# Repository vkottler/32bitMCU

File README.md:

# 32bitMCU
Open source development of microcontroller RTOS, including driver implementations.

## TODO

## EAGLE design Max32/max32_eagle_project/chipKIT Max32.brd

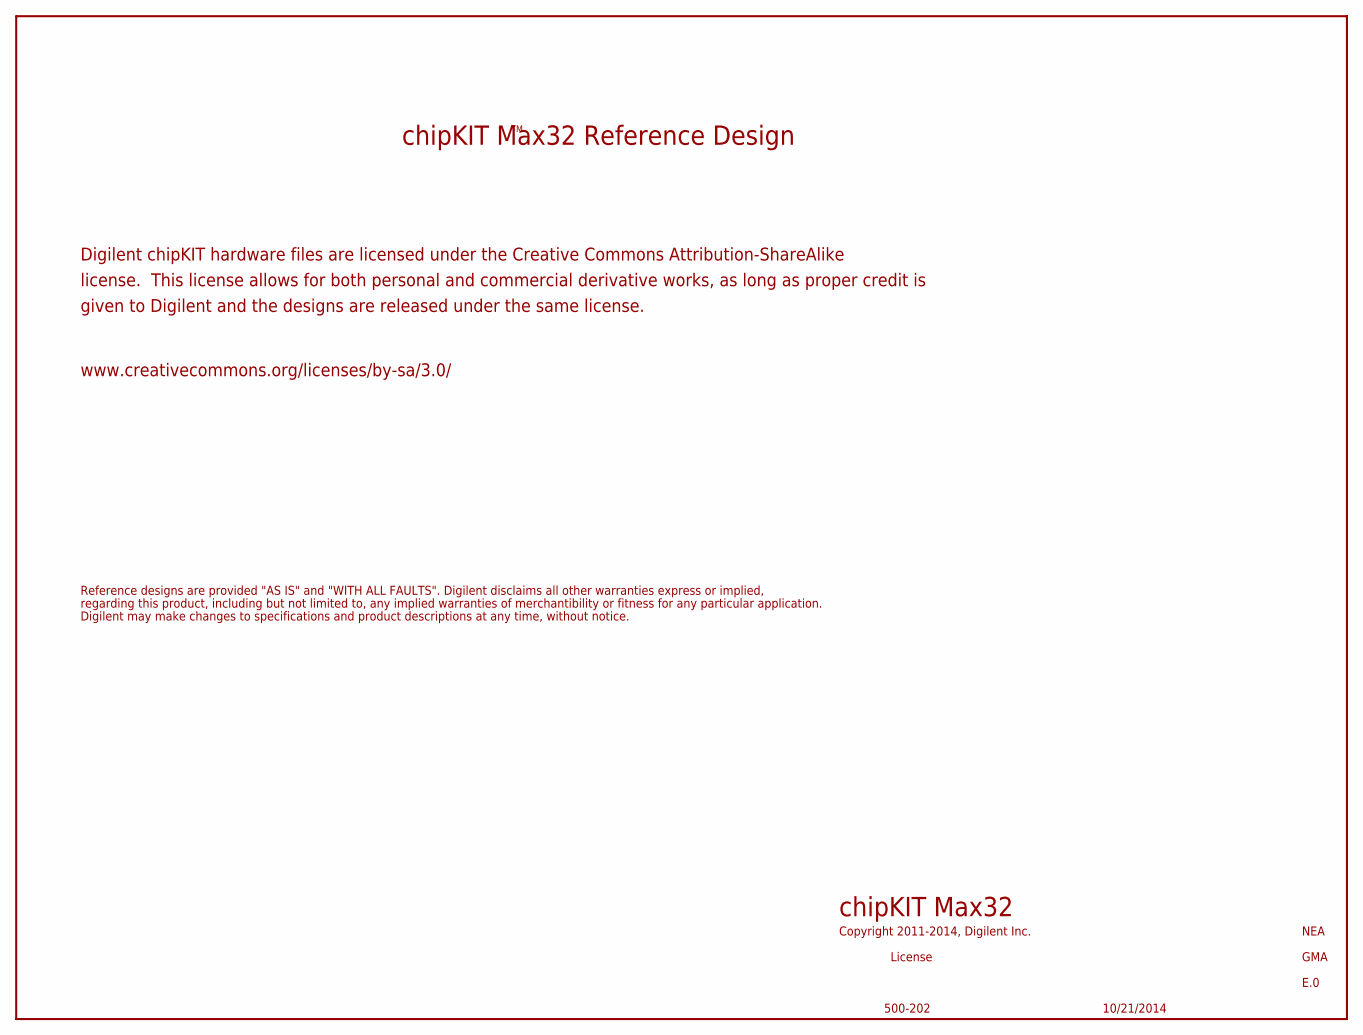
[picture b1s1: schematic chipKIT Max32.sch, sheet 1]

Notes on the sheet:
Digilent chipKIT hardware files are licensed under the Creative Commons Attribution-ShareAlike
license. This license allows for both personal and commercial derivative works, as long as proper credit is
given to Digilent and the designs are released under the same license.
chipKIT Max32 Reference Design
Reference designs are provided "AS IS" and "WITH ALL FAULTS". Digilent disclaims all other warranties express or implied,
regarding this product, including but not limited to, any implied warranties of merchantibility or fitness for any particular application.
Digilent may make changes to specifications and product descriptions at any time, without notice.
www.creativecommons.org/licenses/by-sa/3.0/
Copyright 2011-2014, Digilent Inc.
NEA
GMA
License
500-202
chipKIT Max32
E.0
10/21/2014

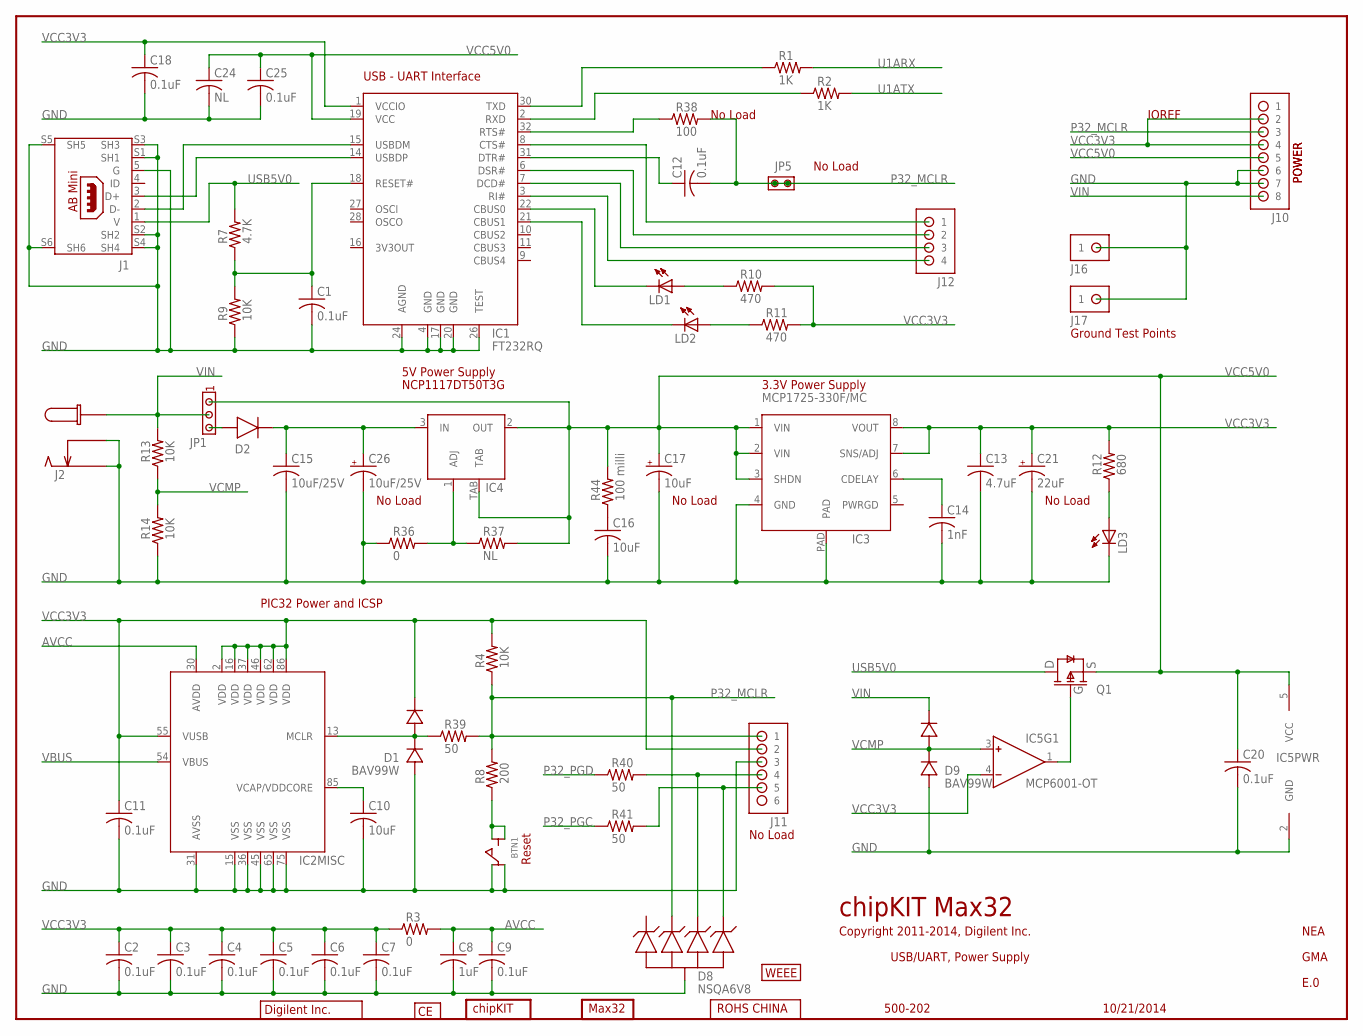
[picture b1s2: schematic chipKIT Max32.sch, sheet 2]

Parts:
BTN1: SW-P8008
C1, C2, C3, C4, C5, C6, C7, C9, C11, C12, C18, C25: 0.1uF; C0402S
C8: 1uF; C0402S
C10, C16: 10uF; C0603S
C13: 4.7uF; C0603S
C14: 1nF; C0402S
C15: 10uF/25V; C0805S
C17: 10uF; CPOL3216
C20: 0.1uF; C0402
C21: 22uF; CPOL3216
C24: NL; C0603S
C26: 10uF/25V; CPOL3216
D1, D9: BAV99W; SOT-323
D2: B220A; SMA
D8: NSQA6V8; SOT-323-5
IC1: FT232RQ; QFN32
IC2: PIC32MX7X5FL-PT; TQ100-PT
IC3: MCP1725-330F/MC; DFN8-MC
IC4: NCP1117DT50T3G; SOT223
IC5: MCP6001-OT; SOT23-5-OT
J1: USB-AB-MINI
J2: CON-COAX-KLD0202-S; KLD-0202S
J10: ST Female; HDR-1X8
J11: No Load; HDR-1X6_OFFSET
J12: HDR-1X4
J16, J17: HDR-1X1
JP1: JPR-1X3
JP5: No Load; JPR-1X2
LD1, LD2, LD3: LED-S0603-RED; D0603
LOGO1: ROHS-CHINA-INV; ROHS_CHINA_INV_LOGO
LOGO2: WEEE-L; WEEE_LOGO2
LOGO4: MAX32_LOGO
LOGO5: CHIPKIT; CHIPKIT_LOGO
LOGO6: CE; CE_LOGO
LOGO7: DIGILENT_INC-BT-1500; DIGILENT_BEYOND_1500_LOGO
Q1: FDN340P; SOT23
R1, R2: 1K; R0402S
R3: 0; R0603
R4, R9, R13, R14: 10K; R0402S
R7: 4.7K; R0402S
R8: 200; R0402S
R10, R11: 470; R0402S
R12: 680; R0402S
R36: 0; R0402S
R37: NL; R0402S
R38: 100; R0402S
R39, R40, R41: 50; R0402S
R44: 100 milli; R0603S

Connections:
AVCC: C8.1, C9.1, IC2.30 (AVDD), R3.2
GND: BTN1.1A, BTN1.2A, C1.2, C2.2, C3.2, C4.2, C5.2, C6.2, C7.2, C8.2, C9.2, C10.2, C11.2, C13.2, C14.2, C15.2, C16.2, C17.-, C18.2, C20.2, C21.-, C24.2, C25.2, C26.-, D1.1 (CAT), D8.2 (COM), D9.1 (CAT), IC1.4 (GND), IC1.17 (GND), IC1.20 (GND), IC1.24 (AGND), IC1.26 (TEST), IC2.15 (VSS), IC2.31 (AVSS), IC2.36 (VSS), IC2.45 (VSS), IC2.65 (VSS), IC2.75 (VSS), IC3.4 (GND), IC3.PAD, IC5.2 (GND), J1.5 (G), J1.S1 (SH1), J1.S2 (SH2), J1.S3 (SH3), J1.S4 (SH4), J1.S5 (SH5), J1.S6 (SH6), J2.2, J2.3, J10.6, J10.7, J11.3, J16.1, J17.1, LD3.C, R9.1, R14.1, R36.1; also elsewhere on the board
unnamed: IC1.14 (USBDP), J1.3 (D+)
unnamed: IC1.15 (USBDM), J1.2 (D-)
unnamed: IC4.1 (ADJ), R36.2, R37.1
unnamed: IC1.30 (TXD), R1.1
unnamed: C10.1, IC2.85 (VCAP/VDDCORE)
unnamed: IC1.2 (RXD), R2.1
unnamed: C12.1, IC1.31 (DTR#)
unnamed: BTN1.1B, BTN1.2B, R8.1
unnamed: IC1.8 (CTS#), J12.1
unnamed: IC1.6 (DSR#), J12.2
unnamed: IC1.7 (DCD#), J12.3
unnamed: IC1.3 (RI#), J12.4
unnamed: IC1.22 (CBUS0), LD1.C
unnamed: IC1.21 (CBUS1), LD2.C
unnamed: LD2.A, R11.1
unnamed: LD1.A, R10.1
unnamed: C14.1, IC3.6 (CDELAY)
unnamed: LD3.A, R12.1
unnamed: D2.A, JP1.3
unnamed: IC5.1 (OUT), Q1.1 (G)
unnamed: C15.1, C26.+, D2.C, IC4.3 (IN)
unnamed: C16.1, R44.1
unnamed: C1.1, IC1.18 (RESET#), R7.1, R9.2
unnamed: D8.4 (D3), J11.4, R40.2
unnamed: IC1.32 (RTS#), R38.1
unnamed: D8.5 (D4), J11.5, R41.2
unnamed: D1.3 (COM), IC2.13 (MCLR), R39.1
P32_MCLR: C12.2, D8.3 (D2), J10.3, J11.1, JP5.1, JP5.2, R4.1, R8.2, R38.2, R39.2
P32_PGC: R41.1; also elsewhere on the board
P32_PGD: R40.1; also elsewhere on the board
U1ARX: R1.2; also elsewhere on the board
U1ATX: R2.2; also elsewhere on the board
USB5V0: J1.1 (V), Q1.3 (D), R7.2
VBUS: IC2.54 (VBUS); also elsewhere on the board
VCC3V3: C2.1, C3.1, C4.1, C5.1, C6.1, C7.1, C11.1, C13.1, C18.1, C21.+, D1.2 (AN), IC1.1 (VCCIO), IC2.2 (VDD), IC2.16 (VDD), IC2.37 (VDD), IC2.46 (VDD), IC2.55 (VUSB), IC2.62 (VDD), IC2.86 (VDD), IC3.7 (SNS/ADJ), IC3.8 (VOUT), IC5.4 (IN-), J10.2, J10.4, J11.2, R3.1, R4.2, R10.2, R11.2, R12.2; also elsewhere on the board
VCC5V0: C17.+, C20.1, C24.1, C25.1, IC1.19 (VCC), IC3.1 (VIN), IC3.2 (VIN), IC3.3 (SHDN), IC4.2 (OUT), IC4.TAB, IC5.5 (VCC), J10.5, JP1.1, Q1.2 (S), R37.2, R44.2; also elsewhere on the board
VCMP: D9.3 (COM), IC5.3 (IN+), R13.1, R14.2
VIN: D9.2 (AN), J2.1, J10.8, JP1.2, R13.2

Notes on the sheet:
Reset
POWER
NCP1117DT50T3G
chipKIT Max32
Copyright 2011-2014, Digilent Inc.
USB/UART, Power Supply
NEA
GMA
E.0
10/21/2014
USB - UART Interface
PIC32 Power and ICSP
5V Power Supply
3.3V Power Supply
500-202
No Load
Ground Test Points
IOREF

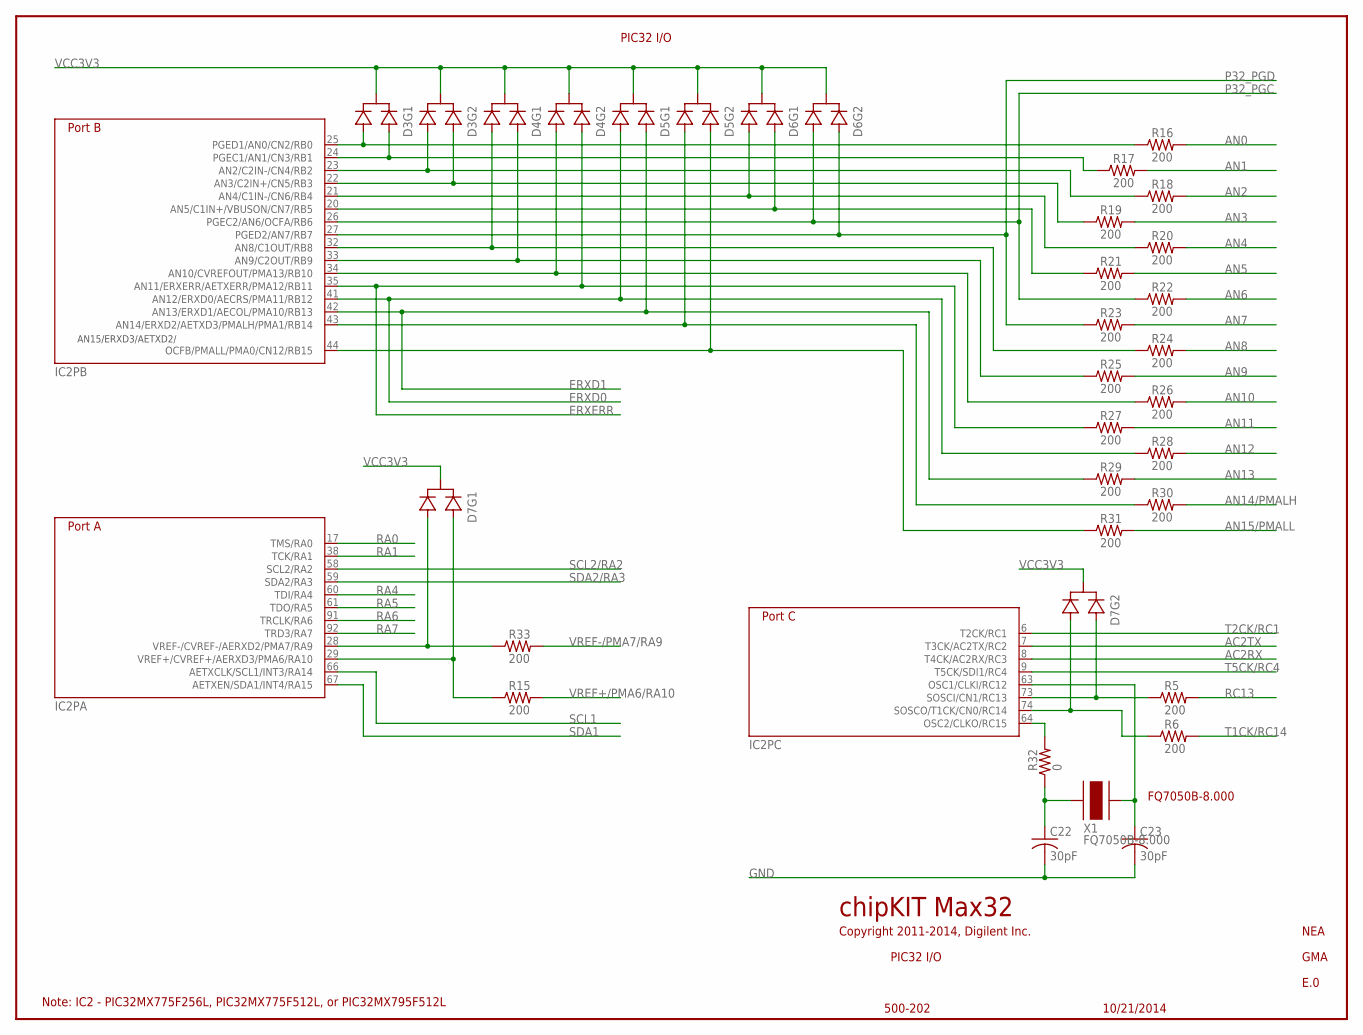
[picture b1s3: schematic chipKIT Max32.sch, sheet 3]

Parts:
C22, C23: 30pF; C0402S
D3, D4, D5, D6, D7: BAV70S; SOT-363
IC2: PIC32MX7X5FL-PT; TQ100-PT
R5, R6, R15, R16, R17, R18, R19, R20, R21, R22, R23, R24, R25, R26, R27, R28, R29, R30, R31, R33: 200; R0402S
R32: 0; R0402S
X1: FQ7050B-8.000; FQ7050B

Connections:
AC2RX: IC2.8 (T4CK/AC2RX/RC3); also elsewhere on the board
AC2TX: IC2.7 (T3CK/AC2TX/RC2); also elsewhere on the board
AN0: R16.2; also elsewhere on the board
AN0-R: D3.1 (A1), IC2.25 (PGED1/AN0/CN2/RB0), R16.1
AN1: R17.2; also elsewhere on the board
AN1-R: D3.2 (A2), IC2.24 (PGEC1/AN1/CN3/RB1), R17.1
AN2: R18.2; also elsewhere on the board
AN3: R19.2; also elsewhere on the board
AN4: R20.2; also elsewhere on the board
AN5: R21.2; also elsewhere on the board
AN6: R22.2; also elsewhere on the board
AN7: R23.2; also elsewhere on the board
AN8: R24.2; also elsewhere on the board
AN9: R25.2; also elsewhere on the board
AN10: R26.2; also elsewhere on the board
AN11: R27.2; also elsewhere on the board
AN12: R28.2; also elsewhere on the board
AN13: R29.2; also elsewhere on the board
AN14/PMALH: R30.2; also elsewhere on the board
AN15/PMALL: R31.2; also elsewhere on the board
ERXD0: D5.1 (A1), IC2.41 (AN12/ERXD0/AECRS/PMA11/RB12), R28.1; also elsewhere on the board
ERXD1: D5.2 (A2), IC2.42 (AN13/ERXD1/AECOL/PMA10/RB13), R29.1; also elsewhere on the board
ERXERR: D4.5 (A2), IC2.35 (AN11/ERXERR/AETXERR/PMA12/RB11), R27.1; also elsewhere on the board
GND: C22.2, C23.2; also elsewhere on the board
unnamed: D7.5 (A2), IC2.73 (SOSCI/CN1/RC13), R5.1
unnamed: D7.4 (A1), IC2.74 (SOSCO/T1CK/CN0/RC14), R6.1
unnamed: D7.1 (A1), IC2.28 (VREF-/CVREF-/AERXD2/PMA7/RA9), R33.1
unnamed: D7.2 (A2), IC2.29 (VREF+/CVREF+/AERXD3/PMA6/RA10), R15.1
unnamed: IC2.64 (OSC2/CLKO/RC15), R32.2
unnamed: C22.1, R32.1, X1.1
unnamed: D3.4 (A1), IC2.23 (AN2/C2IN-/CN4/RB2), R18.1
unnamed: C23.1, IC2.63 (OSC1/CLKI/RC12), X1.3 (2)
unnamed: D3.5 (A2), IC2.22 (AN3/C2IN+/CN5/RB3), R19.1
unnamed: D6.1 (A1), IC2.21 (AN4/C1IN-/CN6/RB4), R20.1
unnamed: D6.2 (A2), IC2.20 (AN5/C1IN+/VBUSON/CN7/RB5), R21.1
unnamed: D4.1 (A1), IC2.32 (AN8/C1OUT/RB8), R24.1
unnamed: D4.2 (A2), IC2.33 (AN9/C2OUT/RB9), R25.1
unnamed: D4.4 (A1), IC2.34 (AN10/CVREFOUT/PMA13/RB10), R26.1
unnamed: D5.4 (A1), IC2.43 (AN14/ERXD2/AETXD3/PMALH/PMA1/RB14), R30.1
unnamed: D5.5 (A2), IC2.44 (OCFB/PMALL/PMA0/CN12/RB15), R31.1
P32_PGC: D6.4 (A1), IC2.26 (PGEC2/AN6/OCFA/RB6), R22.1; also elsewhere on the board
P32_PGD: D6.5 (A2), IC2.27 (PGED2/AN7/RB7), R23.1; also elsewhere on the board
RA0: IC2.17 (TMS/RA0); also elsewhere on the board
RA1: IC2.38 (TCK/RA1); also elsewhere on the board
RA4: IC2.60 (TDI/RA4); also elsewhere on the board
RA5: IC2.61 (TDO/RA5); also elsewhere on the board
RA6: IC2.91 (TRCLK/RA6); also elsewhere on the board
RA7: IC2.92 (TRD3/RA7); also elsewhere on the board
RC13: R5.2; also elsewhere on the board
SCL1: IC2.66 (AETXCLK/SCL1/INT3/RA14); also elsewhere on the board
SCL2/RA2: IC2.58 (SCL2/RA2); also elsewhere on the board
SDA1: IC2.67 (AETXEN/SDA1/INT4/RA15); also elsewhere on the board
SDA2/RA3: IC2.59 (SDA2/RA3); also elsewhere on the board
T1CK/RC14: R6.2; also elsewhere on the board
T2CK/RC1: IC2.6 (T2CK/RC1); also elsewhere on the board
T5CK/RC4: IC2.9 (T5CK/SDI1/RC4); also elsewhere on the board
VCC3V3: D3.3 (K), D3.6 (K), D4.3 (K), D4.6 (K), D5.3 (K), D5.6 (K), D6.3 (K), D6.6 (K), D7.3 (K), D7.6 (K); also elsewhere on the board
VREF+/PMA6/RA10: R15.2; also elsewhere on the board
VREF-/PMA7/RA9: R33.2; also elsewhere on the board

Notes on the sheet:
PIC32 I/O
NEA
Note: IC2 - PIC32MX775F256L, PIC32MX775F512L, or PIC32MX795F512L
500-202
FQ7050B-8.000
GMA
Copyright 2011-2014, Digilent Inc.
chipKIT Max32
E.0
10/21/2014

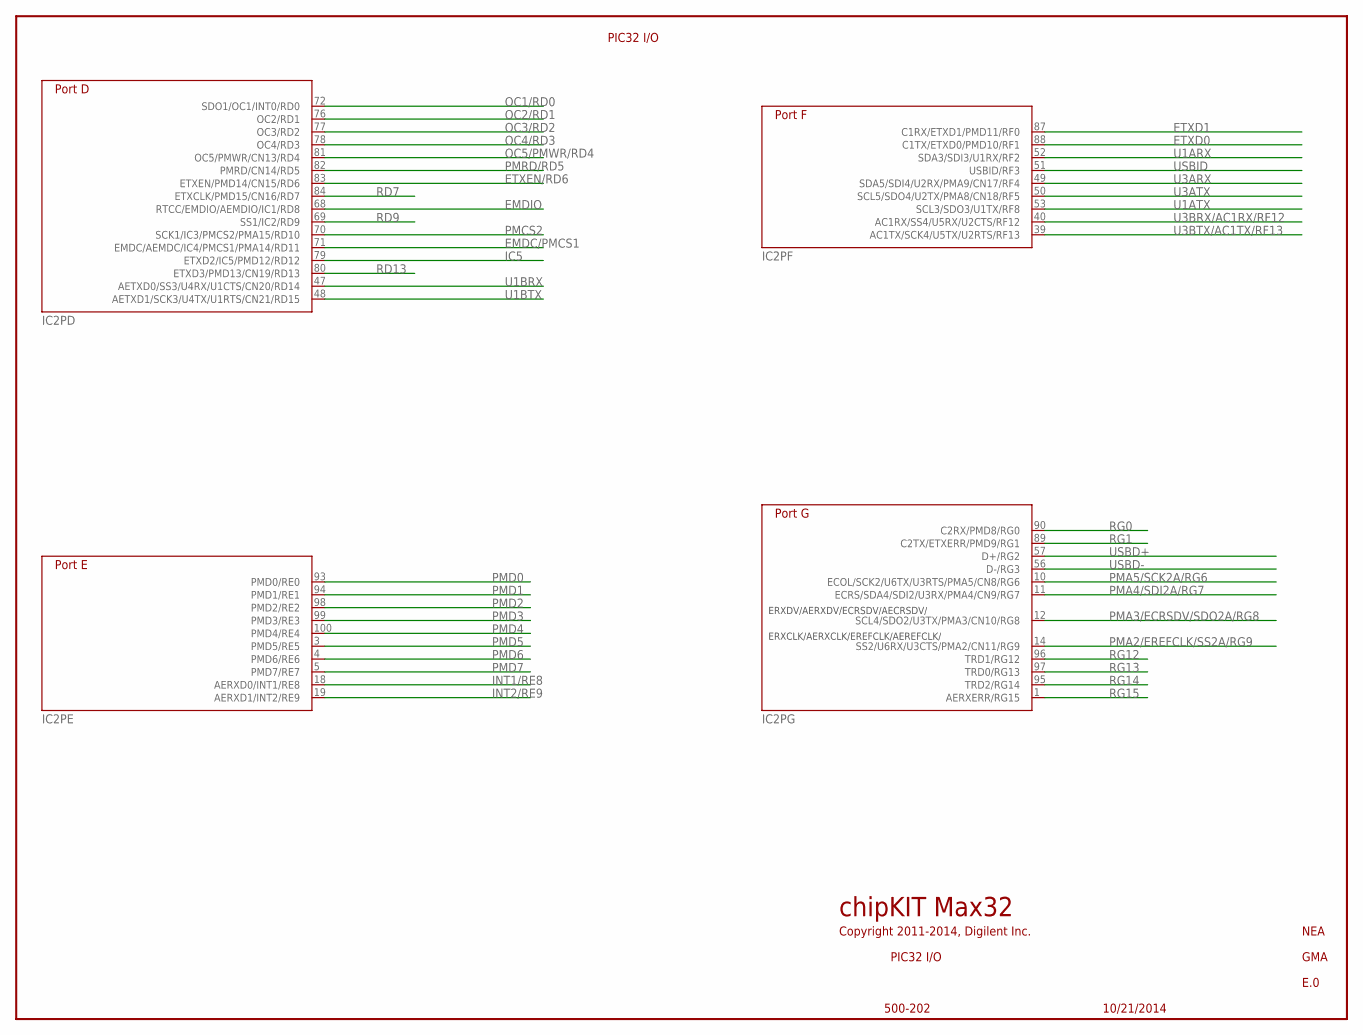
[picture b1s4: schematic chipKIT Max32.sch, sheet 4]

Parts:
IC2: PIC32MX7X5FL-PT; TQ100-PT

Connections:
EMDC/PMCS1: IC2.71 (EMDC/AEMDC/IC4/PMCS1/PMA14/RD11); also elsewhere on the board
EMDIO: IC2.68 (RTCC/EMDIO/AEMDIO/IC1/RD8); also elsewhere on the board
ETXD0: IC2.88 (C1TX/ETXD0/PMD10/RF1); also elsewhere on the board
ETXD1: IC2.87 (C1RX/ETXD1/PMD11/RF0); also elsewhere on the board
ETXEN/RD6: IC2.83 (ETXEN/PMD14/CN15/RD6); also elsewhere on the board
IC5: IC2.79 (ETXD2/IC5/PMD12/RD12); also elsewhere on the board
INT1/RE8: IC2.18 (AERXD0/INT1/RE8); also elsewhere on the board
INT2/RE9: IC2.19 (AERXD1/INT2/RE9); also elsewhere on the board
OC1/RD0: IC2.72 (SDO1/OC1/INT0/RD0); also elsewhere on the board
OC2/RD1: IC2.76 (OC2/RD1); also elsewhere on the board
OC3/RD2: IC2.77 (OC3/RD2); also elsewhere on the board
OC4/RD3: IC2.78 (OC4/RD3); also elsewhere on the board
OC5/PMWR/RD4: IC2.81 (OC5/PMWR/CN13/RD4); also elsewhere on the board
PMA2/EREFCLK/SS2A/RG9: IC2.14 (SS2/U6RX/U3CTS/PMA2/CN11/RG9); also elsewhere on the board
PMA3/ECRSDV/SDO2A/RG8: IC2.12 (SCL4/SDO2/U3TX/PMA3/CN10/RG8); also elsewhere on the board
PMA4/SDI2A/RG7: IC2.11 (ECRS/SDA4/SDI2/U3RX/PMA4/CN9/RG7); also elsewhere on the board
PMA5/SCK2A/RG6: IC2.10 (ECOL/SCK2/U6TX/U3RTS/PMA5/CN8/RG6); also elsewhere on the board
PMCS2: IC2.70 (SCK1/IC3/PMCS2/PMA15/RD10); also elsewhere on the board
PMD0: IC2.93 (PMD0/RE0); also elsewhere on the board
PMD1: IC2.94 (PMD1/RE1); also elsewhere on the board
PMD2: IC2.98 (PMD2/RE2); also elsewhere on the board
PMD3: IC2.99 (PMD3/RE3); also elsewhere on the board
PMD4: IC2.100 (PMD4/RE4); also elsewhere on the board
PMD5: IC2.3 (PMD5/RE5); also elsewhere on the board
PMD6: IC2.4 (PMD6/RE6); also elsewhere on the board
PMD7: IC2.5 (PMD7/RE7); also elsewhere on the board
PMRD/RD5: IC2.82 (PMRD/CN14/RD5); also elsewhere on the board
RD7: IC2.84 (ETXCLK/PMD15/CN16/RD7); also elsewhere on the board
RD9: IC2.69 (SS1/IC2/RD9); also elsewhere on the board
RD13: IC2.80 (ETXD3/PMD13/CN19/RD13); also elsewhere on the board
RG0: IC2.90 (C2RX/PMD8/RG0); also elsewhere on the board
RG1: IC2.89 (C2TX/ETXERR/PMD9/RG1); also elsewhere on the board
RG12: IC2.96 (TRD1/RG12); also elsewhere on the board
RG13: IC2.97 (TRD0/RG13); also elsewhere on the board
RG14: IC2.95 (TRD2/RG14); also elsewhere on the board
RG15: IC2.1 (AERXERR/RG15); also elsewhere on the board
U1ARX: IC2.52 (SDA3/SDI3/U1RX/RF2); also elsewhere on the board
U1ATX: IC2.53 (SCL3/SDO3/U1TX/RF8); also elsewhere on the board
U1BRX: IC2.47 (AETXD0/SS3/U4RX/U1CTS/CN20/RD14); also elsewhere on the board
U1BTX: IC2.48 (AETXD1/SCK3/U4TX/U1RTS/CN21/RD15); also elsewhere on the board
U3ARX: IC2.49 (SDA5/SDI4/U2RX/PMA9/CN17/RF4); also elsewhere on the board
U3ATX: IC2.50 (SCL5/SDO4/U2TX/PMA8/CN18/RF5); also elsewhere on the board
U3BRX/AC1RX/RF12: IC2.40 (AC1RX/SS4/U5RX/U2CTS/RF12); also elsewhere on the board
U3BTX/AC1TX/RF13: IC2.39 (AC1TX/SCK4/U5TX/U2RTS/RF13); also elsewhere on the board
USBD+: IC2.57 (D+/RG2); also elsewhere on the board
USBD-: IC2.56 (D-/RG3); also elsewhere on the board
USBID: IC2.51 (USBID/RF3); also elsewhere on the board

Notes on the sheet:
PIC32 I/O
NEA
500-202
GMA
Copyright 2011-2014, Digilent Inc.
chipKIT Max32
E.0
10/21/2014

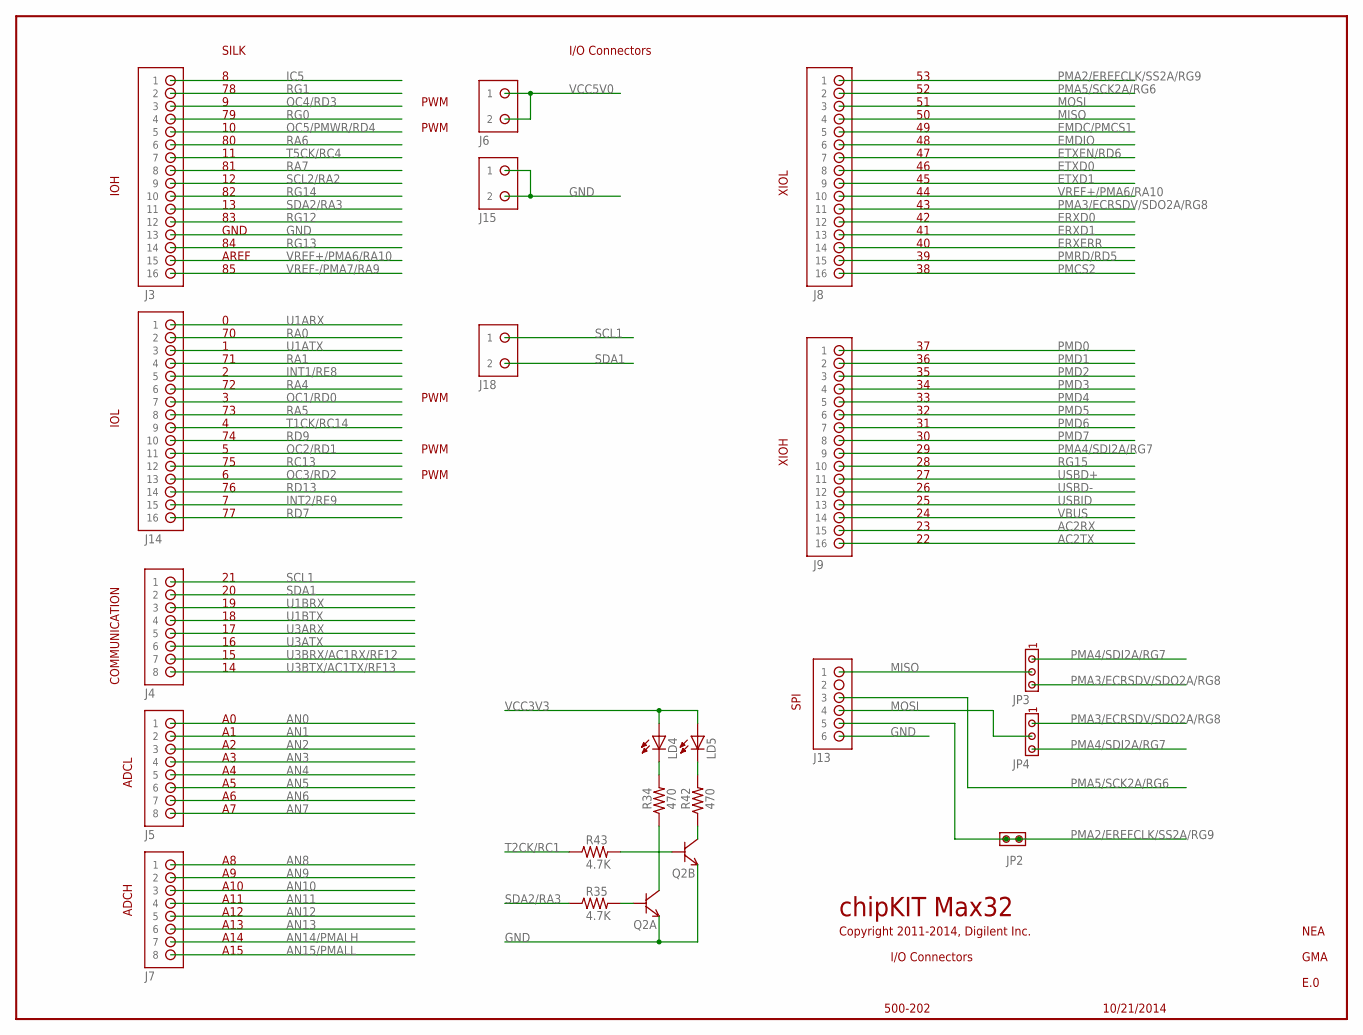
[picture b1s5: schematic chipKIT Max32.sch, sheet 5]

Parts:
J3, J8, J9, J14: HDR-2X8
J4, J5, J7: HDR-1X8
J6, J15: HDR-1X2
J13: HDR-2X3
J18: ST FEMALE; HDR-1X2
JP2: JPR-1X2
JP3, JP4: JPR-1X3
LD4: LED-S0603-GRN; D0603
LD5: LED-S0603; D0603
Q2: MBT3904DW1T1; SOT-363
R34, R42: 470; R0402S
R35, R43: 4.7K; R0402S

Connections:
AC2RX: J9.15; also elsewhere on the board
AC2TX: J9.16; also elsewhere on the board
AN0: J5.1; also elsewhere on the board
AN1: J5.2; also elsewhere on the board
AN2: J5.3; also elsewhere on the board
AN3: J5.4; also elsewhere on the board
AN4: J5.5; also elsewhere on the board
AN5: J5.6; also elsewhere on the board
AN6: J5.7; also elsewhere on the board
AN7: J5.8; also elsewhere on the board
AN8: J7.1; also elsewhere on the board
AN9: J7.2; also elsewhere on the board
AN10: J7.3; also elsewhere on the board
AN11: J7.4; also elsewhere on the board
AN12: J7.5; also elsewhere on the board
AN13: J7.6; also elsewhere on the board
AN14/PMALH: J7.7; also elsewhere on the board
AN15/PMALL: J7.8; also elsewhere on the board
EMDC/PMCS1: J8.5; also elsewhere on the board
EMDIO: J8.6; also elsewhere on the board
ERXD0: J8.12; also elsewhere on the board
ERXD1: J8.13; also elsewhere on the board
ERXERR: J8.14; also elsewhere on the board
ETXD0: J8.8; also elsewhere on the board
ETXD1: J8.9; also elsewhere on the board
ETXEN/RD6: J8.7; also elsewhere on the board
GND: J3.13, J13.6, J15.1, J15.2, Q2.1 (E), Q2.4 (E); also elsewhere on the board
IC5: J3.1; also elsewhere on the board
INT1/RE8: J14.5; also elsewhere on the board
INT2/RE9: J14.15; also elsewhere on the board
MISO: J8.4, J13.1, JP3.2
MOSI: J8.3, J13.4, JP4.2
unnamed: Q2.2 (B), R43.2
unnamed: LD5.C, R42.2
unnamed: Q2.6 (C), R42.1
unnamed: Q2.3 (C), R34.1
unnamed: Q2.5 (B), R35.2
unnamed: LD4.C, R34.2
OC1/RD0: J14.7; also elsewhere on the board
OC2/RD1: J14.11; also elsewhere on the board
OC3/RD2: J14.13; also elsewhere on the board
OC4/RD3: J3.3; also elsewhere on the board
OC5/PMWR/RD4: J3.5; also elsewhere on the board
PMA2/EREFCLK/SS2A/RG9: J8.1, J13.5, JP2.1, JP2.2; also elsewhere on the board
PMA3/ECRSDV/SDO2A/RG8: J8.11, JP3.3, JP4.1; also elsewhere on the board
PMA4/SDI2A/RG7: J9.9, JP3.1, JP4.3; also elsewhere on the board
PMA5/SCK2A/RG6: J8.2, J13.3; also elsewhere on the board
PMCS2: J8.16; also elsewhere on the board
PMD0: J9.1; also elsewhere on the board
PMD1: J9.2; also elsewhere on the board
PMD2: J9.3; also elsewhere on the board
PMD3: J9.4; also elsewhere on the board
PMD4: J9.5; also elsewhere on the board
PMD5: J9.6; also elsewhere on the board
PMD6: J9.7; also elsewhere on the board
PMD7: J9.8; also elsewhere on the board
PMRD/RD5: J8.15; also elsewhere on the board
RA0: J14.2; also elsewhere on the board
RA1: J14.4; also elsewhere on the board
RA4: J14.6; also elsewhere on the board
RA5: J14.8; also elsewhere on the board
RA6: J3.6; also elsewhere on the board
RA7: J3.8; also elsewhere on the board
RC13: J14.12; also elsewhere on the board
RD7: J14.16; also elsewhere on the board
RD9: J14.10; also elsewhere on the board
RD13: J14.14; also elsewhere on the board
RG0: J3.4; also elsewhere on the board
RG1: J3.2; also elsewhere on the board
RG12: J3.12; also elsewhere on the board
RG13: J3.14; also elsewhere on the board
RG14: J3.10; also elsewhere on the board
RG15: J9.10; also elsewhere on the board
SCL1: J4.1, J18.1; also elsewhere on the board
SCL2/RA2: J3.9; also elsewhere on the board
SDA1: J4.2, J18.2; also elsewhere on the board
SDA2/RA3: J3.11, R35.1; also elsewhere on the board
T1CK/RC14: J14.9; also elsewhere on the board
T2CK/RC1: R43.1; also elsewhere on the board
T5CK/RC4: J3.7; also elsewhere on the board
U1ARX: J14.1; also elsewhere on the board
U1ATX: J14.3; also elsewhere on the board
U1BRX: J4.3; also elsewhere on the board
U1BTX: J4.4; also elsewhere on the board
U3ARX: J4.5; also elsewhere on the board
U3ATX: J4.6; also elsewhere on the board
U3BRX/AC1RX/RF12: J4.7; also elsewhere on the board
U3BTX/AC1TX/RF13: J4.8; also elsewhere on the board
USBD+: J9.11; also elsewhere on the board
USBD-: J9.12; also elsewhere on the board
USBID: J9.13; also elsewhere on the board
VBUS: J9.14; also elsewhere on the board
VCC3V3: LD4.A, LD5.A; also elsewhere on the board
VCC5V0: J6.1, J6.2; also elsewhere on the board
VREF+/PMA6/RA10: J3.15, J8.10; also elsewhere on the board
VREF-/PMA7/RA9: J3.16; also elsewhere on the board

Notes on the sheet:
IOL
IOH
COMMUNICATION
ADCL
ADCH
XIOL
XIOH
SPI
PWM
I/O Connectors
NEA
500-202
GMA
Copyright 2011-2014, Digilent Inc.
chipKIT Max32
AREF
GND
A10
A11
SILK
A12
A13
A14
A15
E.0
10/21/2014

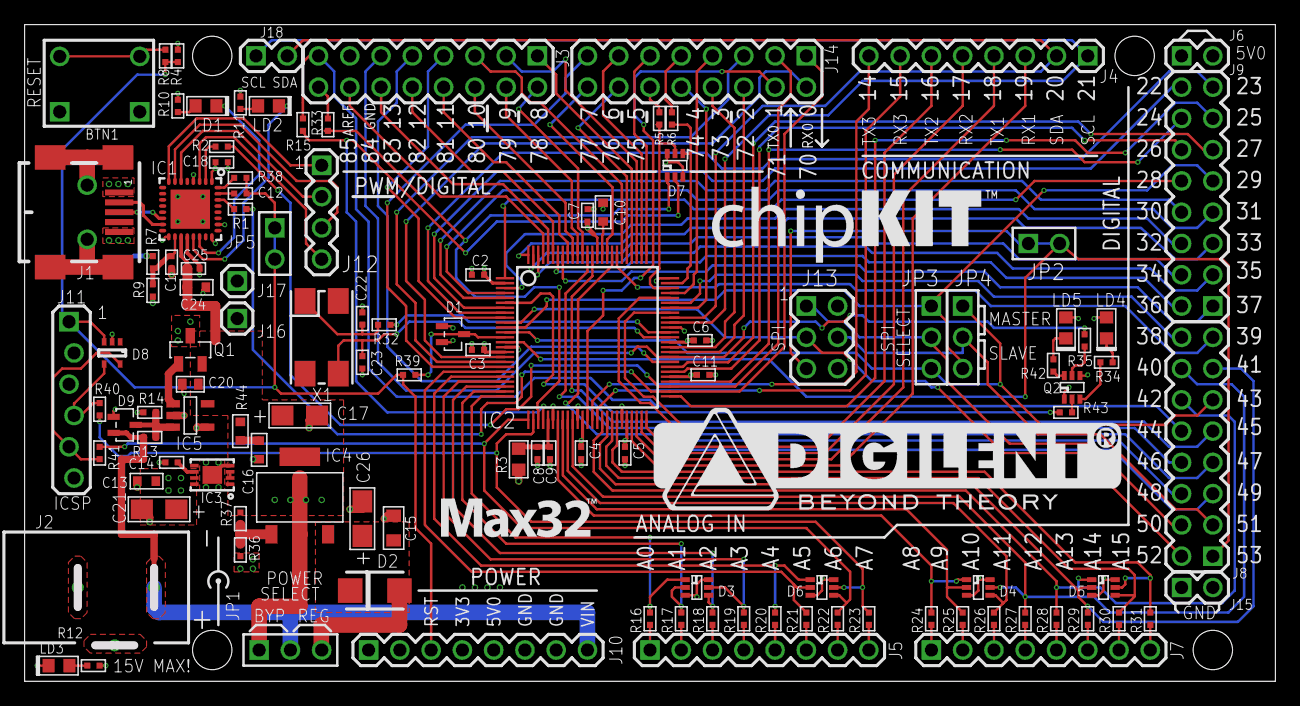
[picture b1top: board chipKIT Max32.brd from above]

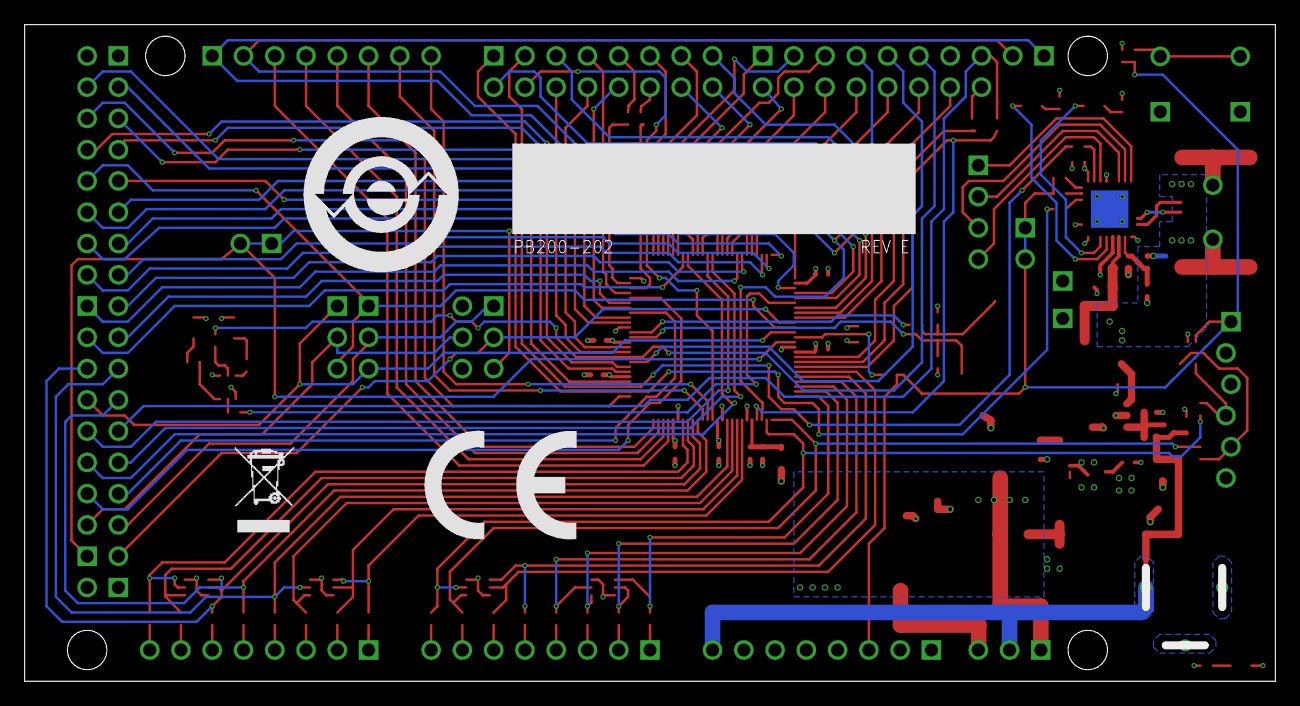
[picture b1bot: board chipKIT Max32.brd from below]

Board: 4 copper layers, 101.6 x 53.3 mm, 121 parts (3 on the bottom side), 148 nets.

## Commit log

2017-03-10 adding documentation
2017-05-08 adding new skeleton project and documentation
2017-05-09 getting rid of object files
2017-05-09 fixing up project
2017-05-09 messing around with project still
2017-05-10 adding some docs, trying to figure out how to start programming this thing
2017-05-11 adding touch screen datasheet
2017-05-14 updating project config
2017-05-15 oscillator configuration complete
2017-05-25 this needs work
